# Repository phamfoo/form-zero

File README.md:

# Form Zero
> Gasket mounted ortholinear keyboard

## Introduction
This project aims to provide an ergonomic keyboard that looks nice while also including the neat features that you'd find in custom mechanical keyboards:

- Gasket-mounted.
- Hotswap PCB.
- Clean and minimal design.

It's also designed to be put together by hobbyists, so all the parts can be easily sourced and only basic soldering skills are required.

## Build guide
See [build](/build)

## Thanks
[JLCPCB](https://jlcpcb.com/) for providing the keyboard plate, 3D printed case, and PCBs for this project. If you're looking to build your own board, I highly recommend their services.

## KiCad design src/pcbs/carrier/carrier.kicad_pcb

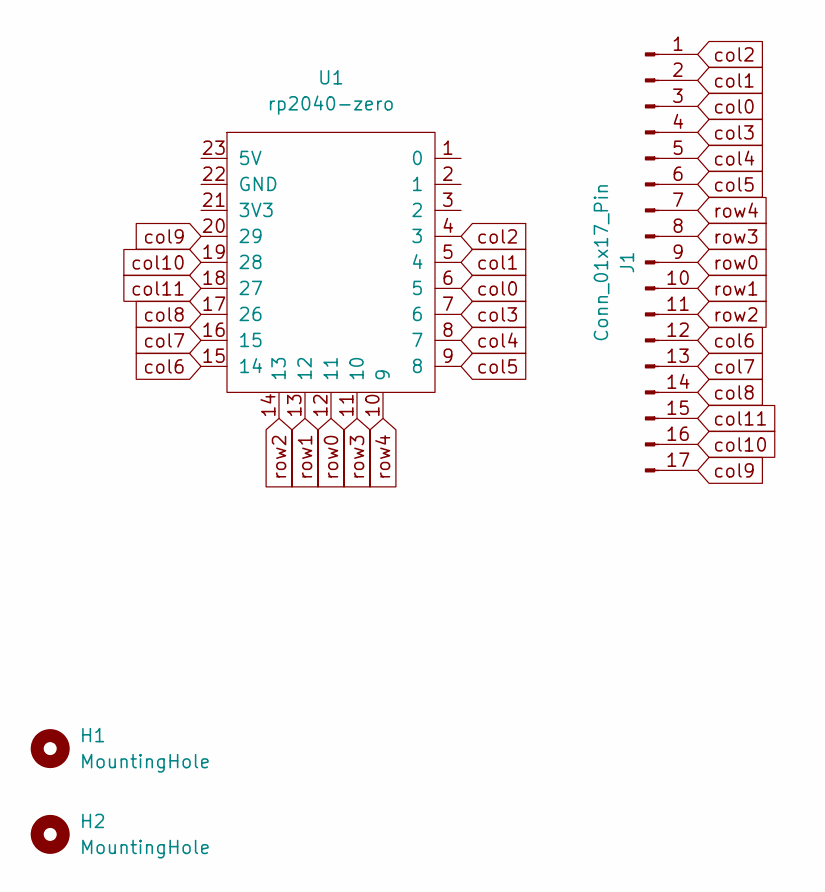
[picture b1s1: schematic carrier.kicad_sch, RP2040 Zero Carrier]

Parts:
H1, H2: MountingHole; MountingHole_2.2mm_M2
J1: Conn_01x17_Pin; PinHeader_1x17_P2.54mm_Vertical
U1: rp2040-zero; rp2040-zero-tht

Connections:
col0: J1.3, U1.6 (5)
col1: J1.2, U1.5 (4)
col2: J1.1, U1.4 (3)
col3: J1.4, U1.7 (6)
col4: J1.5, U1.8 (7)
col5: J1.6, U1.9 (8)
col6: J1.12, U1.15 (14)
col7: J1.13, U1.16 (15)
col8: J1.14, U1.17 (26)
col9: J1.17, U1.20 (29)
col10: J1.16, U1.19 (28)
col11: J1.15, U1.18 (27)
row0: J1.9, U1.12 (11)
row1: J1.10, U1.13 (12)
row2: J1.11, U1.14 (13)
row3: J1.8, U1.11 (10)
row4: J1.7, U1.10 (9)

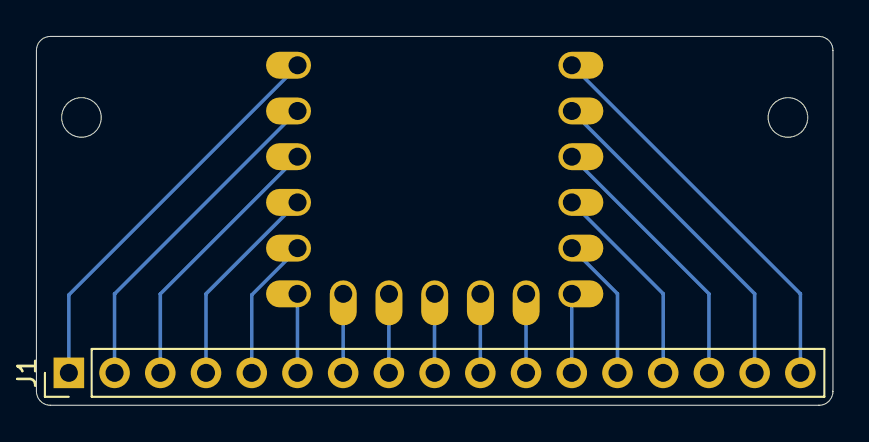
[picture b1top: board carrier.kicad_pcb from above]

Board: 2 copper layers, 44.2 x 20.5 mm, 4 parts (1 on the bottom side), 17 nets.

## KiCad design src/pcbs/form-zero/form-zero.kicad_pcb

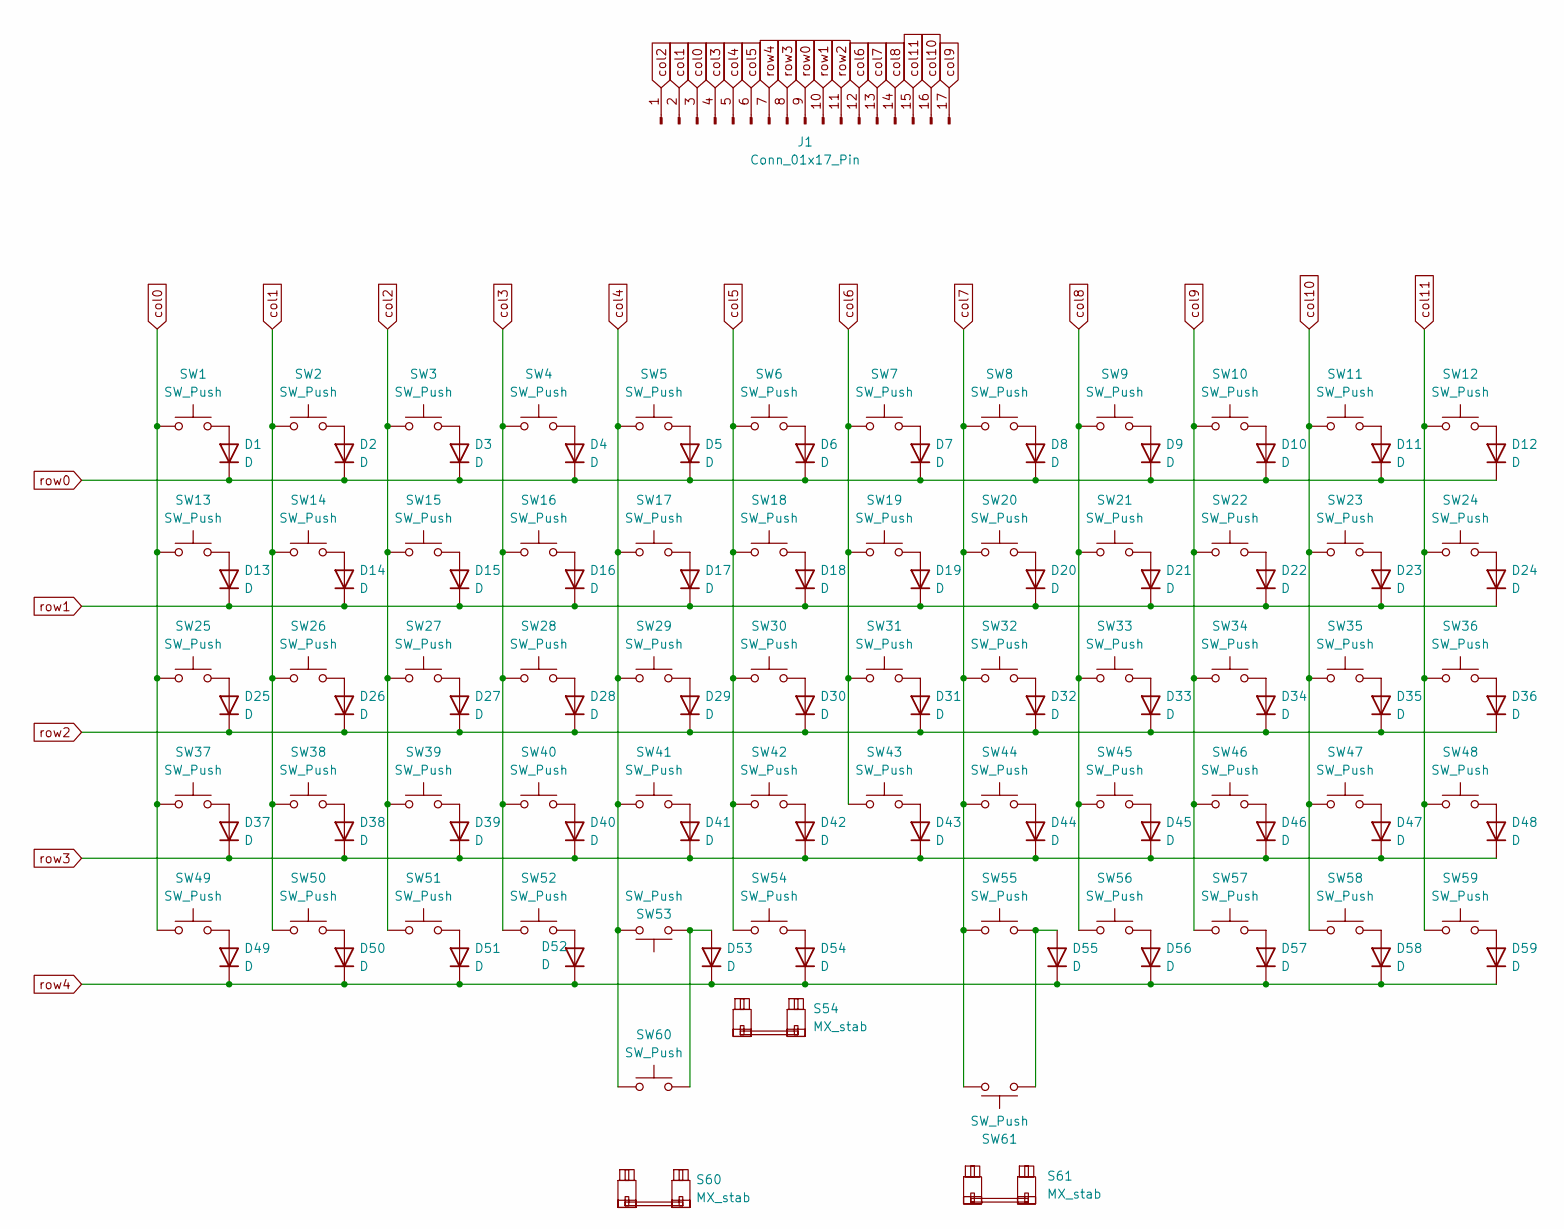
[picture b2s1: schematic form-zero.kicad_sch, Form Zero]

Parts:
D1, D2, D3, D4, D5, D6, D7, D8, D9, D10, D11, D12, D13, D14, D15, D16, D17, D18, D19, D20, D21, D22, D23, D24, D25, D26, D27, D28, D29, D30, D31, D32, D33, D34, D35, D36, D37, D38, D39, D40, D41, D42, D43, D44, D45, D46, D47, D48, D49, D50, D51, D52, D53, D54, D55, D56, D57, D58, D59: D; D3_TH_SMD_v2
J1: Conn_01x17_Pin; PinHeader_1x17_P2.54mm_Vertical
S54, S60, S61: MX_stab; STAB_MX_2u
SW1, SW2, SW3, SW4, SW5, SW6, SW7, SW8, SW9, SW10, SW11, SW12, SW13, SW14, SW15, SW16, SW17, SW18, SW19, SW20, SW21, SW22, SW23, SW24, SW25, SW26, SW27, SW28, SW29, SW30, SW31, SW32, SW33, SW34, SW35, SW36, SW37, SW38, SW39, SW40, SW41, SW42, SW43, SW44, SW45, SW46, SW47, SW48, SW49, SW50, SW51, SW52, SW53, SW54, SW55, SW56, SW57, SW58, SW59, SW60, SW61: SW_Push; SW_MX_HS_CPG151101S11_1u

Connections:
unnamed: D1.2 (A), SW1.2
unnamed: D2.2 (A), SW2.2
unnamed: D3.2 (A), SW3.2
unnamed: D4.2 (A), SW4.2
unnamed: D5.2 (A), SW5.2
unnamed: D6.2 (A), SW6.2
unnamed: D7.2 (A), SW7.2
unnamed: D8.2 (A), SW8.2
unnamed: D9.2 (A), SW9.2
unnamed: D10.2 (A), SW10.2
unnamed: D11.2 (A), SW11.2
unnamed: D12.2 (A), SW12.2
unnamed: D13.2 (A), SW13.2
unnamed: D14.2 (A), SW14.2
unnamed: D15.2 (A), SW15.2
unnamed: D16.2 (A), SW16.2
unnamed: D17.2 (A), SW17.2
unnamed: D18.2 (A), SW18.2
unnamed: D19.2 (A), SW19.2
unnamed: D20.2 (A), SW20.2
unnamed: D21.2 (A), SW21.2
unnamed: D22.2 (A), SW22.2
unnamed: D23.2 (A), SW23.2
unnamed: D24.2 (A), SW24.2
unnamed: D25.2 (A), SW25.2
unnamed: D26.2 (A), SW26.2
unnamed: D27.2 (A), SW27.2
unnamed: D28.2 (A), SW28.2
unnamed: D29.2 (A), SW29.2
unnamed: D30.2 (A), SW30.2
unnamed: D31.2 (A), SW31.2
unnamed: D32.2 (A), SW32.2
unnamed: D33.2 (A), SW33.2
unnamed: D34.2 (A), SW34.2
unnamed: D35.2 (A), SW35.2
unnamed: D36.2 (A), SW36.2
unnamed: D37.2 (A), SW37.2
unnamed: D38.2 (A), SW38.2
unnamed: D39.2 (A), SW39.2
unnamed: D40.2 (A), SW40.2
unnamed: D41.2 (A), SW41.2
unnamed: D42.2 (A), SW42.2
unnamed: D43.2 (A), SW43.2
unnamed: D44.2 (A), SW44.2
unnamed: D45.2 (A), SW45.2
unnamed: D46.2 (A), SW46.2
unnamed: D47.2 (A), SW47.2
unnamed: D48.2 (A), SW48.2
unnamed: D49.2 (A), SW49.2
unnamed: D50.2 (A), SW50.2
unnamed: D51.2 (A), SW51.2
unnamed: D52.2 (A), SW52.2
unnamed: D53.2 (A), SW53.1, SW60.2
unnamed: D54.2 (A), SW54.2
unnamed: D55.2 (A), SW55.2, SW61.1
unnamed: D56.2 (A), SW56.2
unnamed: D57.2 (A), SW57.2
unnamed: D58.2 (A), SW58.2
unnamed: D59.2 (A), SW59.2
col0: J1.3, SW1.1, SW13.1, SW25.1, SW37.1, SW49.1
col1: J1.2, SW2.1, SW14.1, SW26.1, SW38.1, SW50.1
col2: J1.1, SW3.1, SW15.1, SW27.1, SW39.1, SW51.1
col3: J1.4, SW4.1, SW16.1, SW28.1, SW40.1, SW52.1
col4: J1.5, SW5.1, SW17.1, SW29.1, SW41.1, SW53.2, SW60.1
col5: J1.6, SW6.1, SW18.1, SW30.1, SW42.1, SW54.1
col6: J1.12, SW7.1, SW19.1, SW31.1, SW43.1
col7: J1.13, SW8.1, SW20.1, SW32.1, SW44.1, SW55.1, SW61.2
col8: J1.14, SW9.1, SW21.1, SW33.1, SW45.1, SW56.1
col9: J1.17, SW10.1, SW22.1, SW34.1, SW46.1, SW57.1
col10: J1.16, SW11.1, SW23.1, SW35.1, SW47.1, SW58.1
col11: J1.15, SW12.1, SW24.1, SW36.1, SW48.1, SW59.1
row0: D1.1 (K), D2.1 (K), D3.1 (K), D4.1 (K), D5.1 (K), D6.1 (K), D7.1 (K), D8.1 (K), D9.1 (K), D10.1 (K), D11.1 (K), D12.1 (K), J1.9
row1: D13.1 (K), D14.1 (K), D15.1 (K), D16.1 (K), D17.1 (K), D18.1 (K), D19.1 (K), D20.1 (K), D21.1 (K), D22.1 (K), D23.1 (K), D24.1 (K), J1.10
row2: D25.1 (K), D26.1 (K), D27.1 (K), D28.1 (K), D29.1 (K), D30.1 (K), D31.1 (K), D32.1 (K), D33.1 (K), D34.1 (K), D35.1 (K), D36.1 (K), J1.11
row3: D37.1 (K), D38.1 (K), D39.1 (K), D40.1 (K), D41.1 (K), D42.1 (K), D43.1 (K), D44.1 (K), D45.1 (K), D46.1 (K), D47.1 (K), D48.1 (K), J1.8
row4: D49.1 (K), D50.1 (K), D51.1 (K), D52.1 (K), D53.1 (K), D54.1 (K), D55.1 (K), D56.1 (K), D57.1 (K), D58.1 (K), D59.1 (K), J1.7

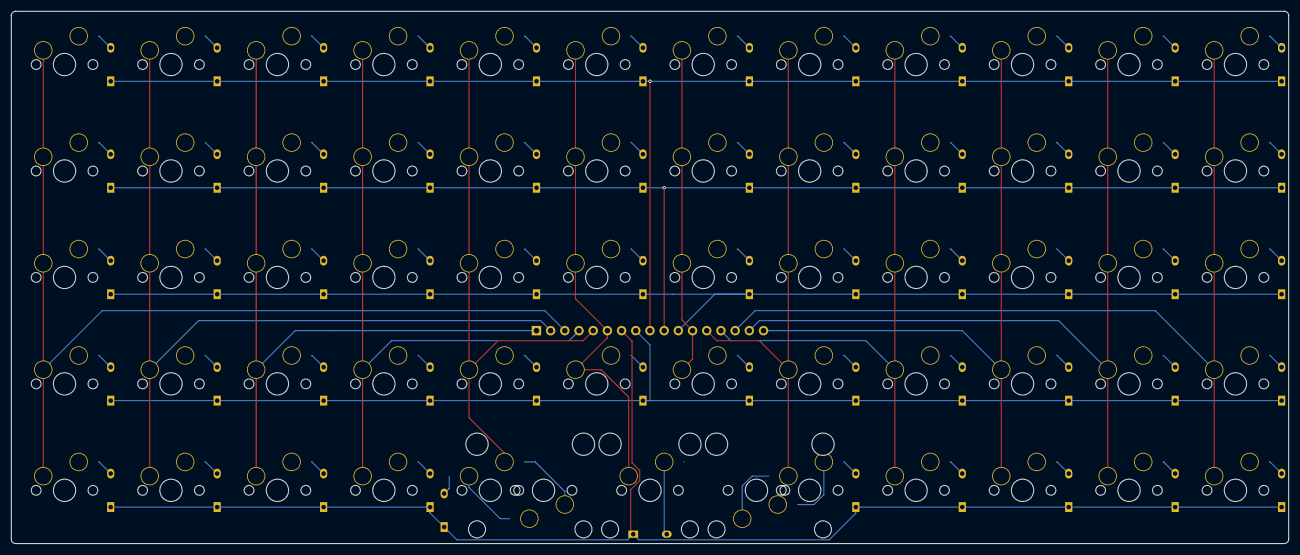
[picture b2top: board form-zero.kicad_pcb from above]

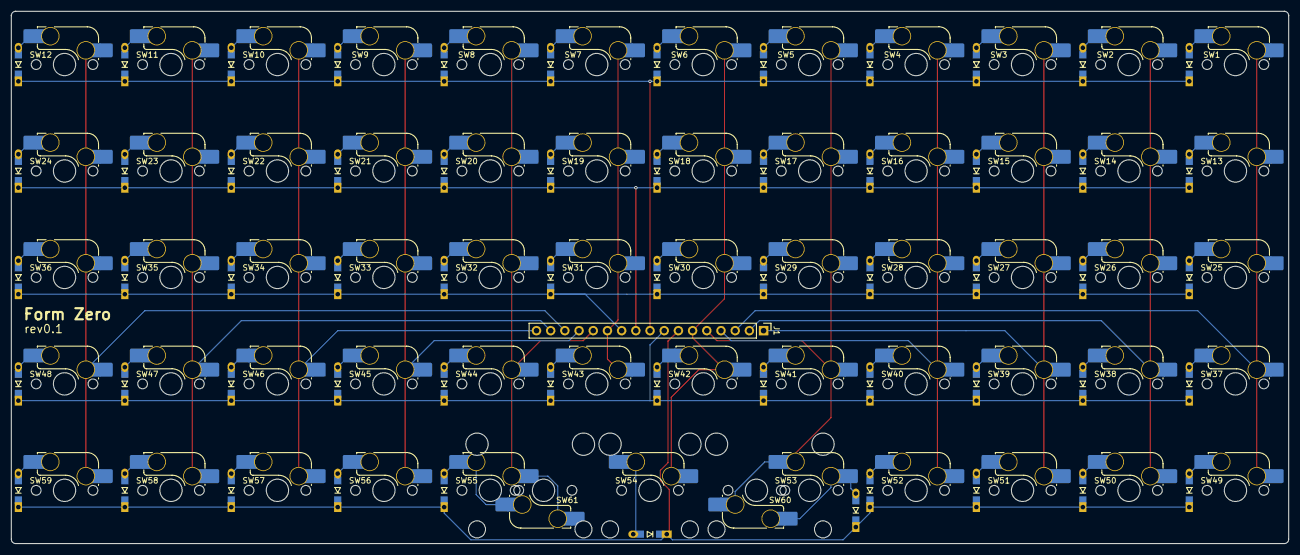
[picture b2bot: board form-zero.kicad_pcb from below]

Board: 2 copper layers, 228.6 x 95.2 mm, 124 parts (121 on the bottom side), 76 nets.

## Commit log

2024-06-18 Add pcbs
2024-06-19 Add case and plate files
2024-06-19 Add build files
2024-06-22 Add build guide
2024-06-22 Add LICENSE
2024-06-24 Add README
2024-06-24 Add firmware
2024-06-25 Update build guide
